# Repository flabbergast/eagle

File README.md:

# flabbergast's [EAGLE](http://www.cadsoftusa.com/eagle-pcb-design-software/?language=en) PCB files

Currently, the following PCBs are here:

## X-A4U stick (rev1 and rev2.1)

An USB stick with atxmega128a4u, RGB LED, microSD socket and 2 buttons.
More details [here](https://flabbergast.github.io/x-a4u-r2/).

## little2wire

My SMD take on [Little Wire](http://littlewire.cc). Optionally 3V3
operation, USB-A or mini or micro USB socket. Webpage
[here](https://flabbergast.github.io/l2w/).

## [AVR stick] microSD + ATMEL EEPROM shield

A shield for matrixstorm's [AVR stick], with micro SD, SOIC-8 (JEDEC)
I2C EEPROM landing and a proto area.
A more detailed writeup is
[here](http://174763.calepin.co/uSD-shield-1.html).

Fits Sparkfun's [microSD socket](https://www.sparkfun.com/products/127),
a variety of ATMEL (or others') I2C EEPROMs (including crypto chips like
[ATSHA204], [ATAES132] or [ATECC108] in SOIC-8 package). One button
(also from [Sparkfun](https://www.sparkfun.com/products/8720)), one LED.
The smaller parts are SMD 1206.

## Small UEXT board with microSD and I2C EEPROM

A simple [UEXT] board, with the same microSD socket from Sparkfun, and a
SOIC-8 I2C EEPROM landing. Note that the boards from [Olimex] with UEXT
already have pull-ups on I2C signals, so these are not needed if it
should be used with them.

## Various breakout_ boards

These are basic breakouts for some ARM chips. Minimal (recommended) extra parts. For photos and some comments see [this post](https://flabbergast.github.io/posts/arm-breakouts/).

## blackmagic-hw

A variation on [Black Magic Probe] Mini V1, based off of [Richard Meadows' variation](https://github.com/richardeoin/blackmagic-hardware/).
See README in the subdirectory for more info.

[AVR stick]: http://matrixstorm.com/avr/avrstick/
[ATSHA204]: http://www.atmel.com/devices/atsha204.aspx
[ATAES132]: http://www.atmel.com/devices/ataes132.aspx
[ATECC108]: http://www.atmel.com/devices/atecc108.aspx
[Olimex]: https://www.olimex.com/
[UEXT]: https://www.olimex.com/Products/Modules/
[Black Magic Probe]: https://black-magic.org/

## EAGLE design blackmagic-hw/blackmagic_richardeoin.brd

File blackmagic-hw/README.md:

# A variation of Black Magic Probe mini V1.0

Started with [Richard Meadows' modification](https://github.com/richardeoin/blackmagic-hardware/) of BMPMV1, summary of that is below.

On top of that, no electrical modifications, only added an option to solder USB micro socket instead of USB mini; and the 10 pin programming header is now through-hole.

# Original README from Richard Meadows

This variant attempts to be as faithful to the Blackmagic mini as
possible, but also has several differences. This board has been built
and functions.

## Details

* The schematic and board have both been designed using Cadsoft EAGLE
  v6.4.0.

* The board size is 40mm x 16mm.

* The programming connector is an ARM 10-PIN Interface as described
  [here](http://www.keil.com/support/man/docs/ulink2/ulink2_hw_connectors.htm).

## Differences

### Uses 0603 [1608 Metric] components

The layout is intended for reflow soldering.

### Includes Level Translator

This board incorporates the same level translator used in the
full-sized Blackmagic, so it can be used to safely program 2.7V or
1.8V systems.

### USART Connector

The STM32F103's USART1 peripheral is broken out into a 0.1"
header. The hole centres are
[slightly offset to allow a press-fit](https://www.sparkfun.com/tutorials/114).

### BOOT0 Button

As well as the standard button for entering USB DFU mode, this variant
also provides a button for pulling the BOOT0 pin high to activate the
STM32 SystemMemory bootloader. Hold this button when plugging in the
module to enter then bootloader mode, over USART1.

This is useful for programming a brand new or 'bricked' blackmagic
with the DFU firmware, the standard DFU mode
should be used for regular firmware updates.

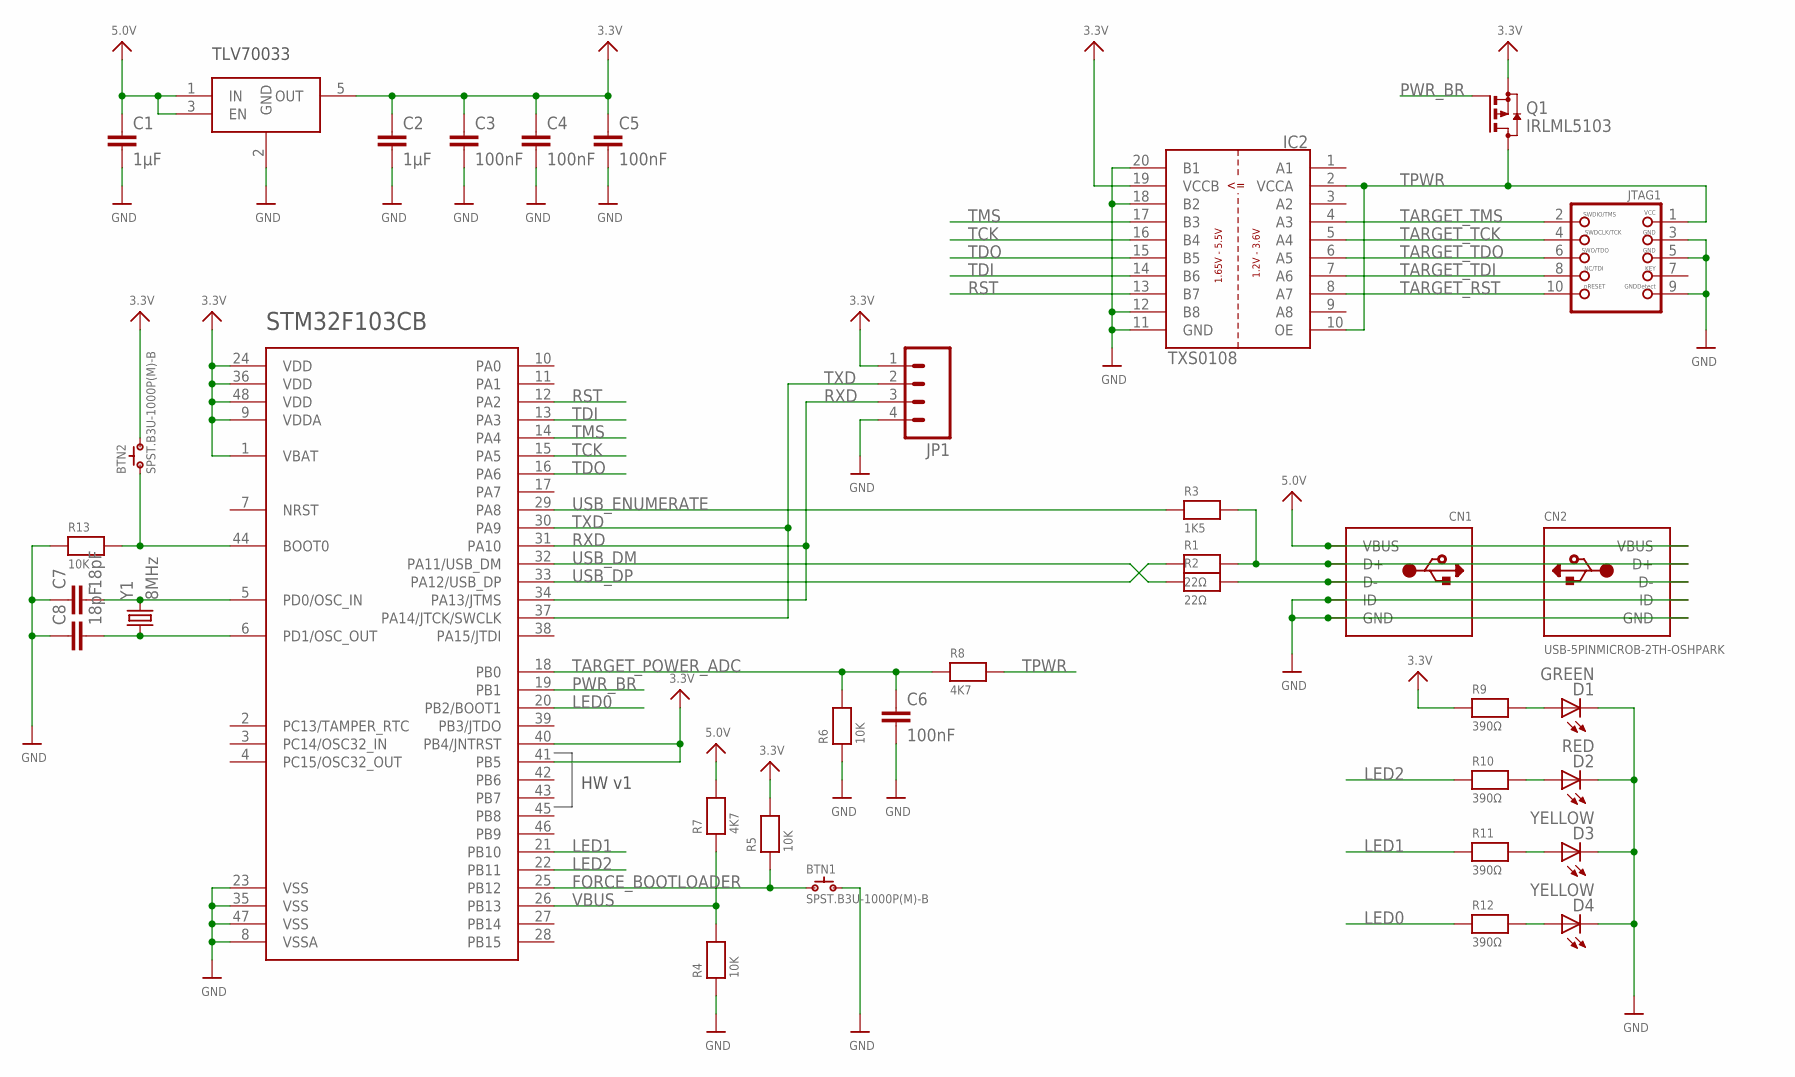
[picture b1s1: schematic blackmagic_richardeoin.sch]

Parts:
BTN1, BTN2: SPST.B3U-1000P(M)-B; B3U-1000P(M)-B
C1, C2: 1µF; C0603K
C3, C4, C5, C6: 100nF; C0603K
C7, C8: 18pF; C0603K
CN1: USBMINIB; USB-MINIB
CN2: USB-5PINMICROB-2TH-OSHPARK; USB-MICROB-2TH-OSHPARK
D1: GREEN; CHIPLED_0603
D2: RED; CHIPLED_0603
D3, D4: YELLOW; CHIPLED_0603
IC1: STM32F_48PIN; TQFP48
IC2: TXS0108; TSSOP20
IC3: TLV70033DCK; SC70-5L
JP1: M04LOCK; 1X04_LOCK
JTAG1: JTAG-CORTEXM3TH; 2X05_1.27MM_TH
Q1: IRLML5103; SOT23
R1, R2: 22Ω; 0603-MINI
R3: 1K5; 0603-MINI
R4, R5, R6, R13: 10K; 0603-MINI
R7, R8: 4K7; 0603-MINI
R9, R10, R11, R12: 390Ω; 0603-MINI
Y1: 8MHz; CRYSTAL-SMD-5X3

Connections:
3.3V: BTN2.2, C2.1, C3.1, C4.1, C5.1, IC1.1 (VBAT), IC1.9 (VDDA), IC1.24 (VDD), IC1.36 (VDD), IC1.40 (PB4/JNTRST), IC1.41 (PB5), IC1.48 (VDD), IC2.19 (VCCB), IC3.5 (OUT), JP1.1, Q1.2 (S), R5.2, R9.1
5.0V: C1.1, CN1.VBUS, CN2.VBUS, IC3.1 (IN), IC3.3 (EN), R7.2
BOOT0: BTN2.1, IC1.44 (BOOT0), R13.2
D+: CN1.D+, CN2.D+, R1.2, R3.2
D-: CN1.D-, CN2.D-, R2.2
FORCE_BOOTLOADER: BTN1.1, IC1.25 (PB12), R5.1
GND: BTN1.2, C1.2, C2.2, C3.2, C4.2, C5.2, C6.2, C7.1, C8.1, CN1.GND, CN1.ID, CN2.GND, CN2.ID, D1.C, D2.C, D3.C, D4.C, IC1.8 (VSSA), IC1.23 (VSS), IC1.35 (VSS), IC1.47 (VSS), IC2.11 (GND), IC2.12 (B8), IC2.18 (B2), IC2.20 (B1), IC3.2 (GND), JP1.4, JTAG1.3, JTAG1.5, JTAG1.9, R4.1, R6.1, R13.1
LED0: IC1.20 (PB2/BOOT1), R12.1
LED1: IC1.21 (PB10), R11.1
LED2: IC1.22 (PB11), R10.1
LPC_XTAL2: C8.2, IC1.6 (PD1/OSC_OUT), Y1.1
unnamed: D2.A, R10.2
unnamed: D1.A, R9.2
unnamed: D3.A, R11.2
unnamed: D4.A, R12.2
OSC_IN: C7.2, IC1.5 (PD0/OSC_IN), Y1.3 (2)
PWR_BR: IC1.19 (PB1), Q1.1 (G)
RST: IC1.12 (PA2), IC2.13 (B7)
RXD: IC1.31 (PA10), IC1.34 (PA13/JTMS), JP1.3
TARGET_POWER_ADC: C6.1, IC1.18 (PB0), R6.2, R8.1
TARGET_RST: IC2.8 (A7), JTAG1.10
TARGET_TCK: IC2.5 (A4), JTAG1.4
TARGET_TDI: IC2.7 (A6), JTAG1.8
TARGET_TDO: IC2.6 (A5), JTAG1.6
TARGET_TMS: IC2.4 (A3), JTAG1.2
TCK: IC1.15 (PA5), IC2.16 (B4)
TDI: IC1.13 (PA3), IC2.14 (B6)
TDO: IC1.16 (PA6), IC2.15 (B5)
TMS: IC1.14 (PA4), IC2.17 (B3)
TPWR: IC2.2 (VCCA), IC2.10 (OE), JTAG1.1, Q1.3 (D), R8.2
TXD: IC1.30 (PA9), IC1.37 (PA14/JTCK/SWCLK), JP1.2
USB_DM: IC1.32 (PA11/USB_DM), R2.1
USB_DP: IC1.33 (PA12/USB_DP), R1.1
USB_ENUMERATE: IC1.29 (PA8), R3.1
VBUS: IC1.26 (PB13), R4.2, R7.1

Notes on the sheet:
STM32F103CB
HW v1
TLV70033

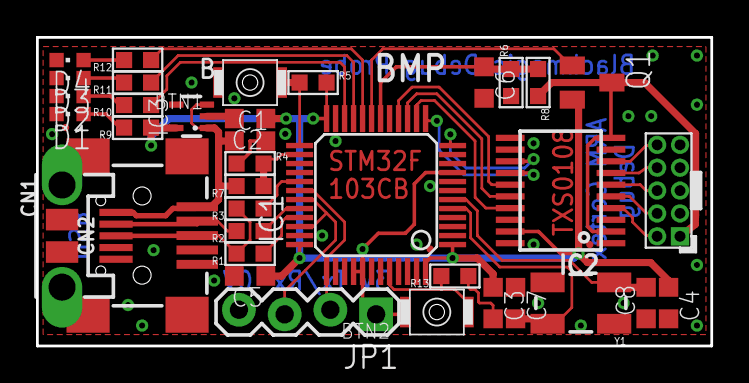
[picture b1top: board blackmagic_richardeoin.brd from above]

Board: 2 copper layers, 37.5 x 17.1 mm, 36 parts (0 on the bottom side), 35 nets.

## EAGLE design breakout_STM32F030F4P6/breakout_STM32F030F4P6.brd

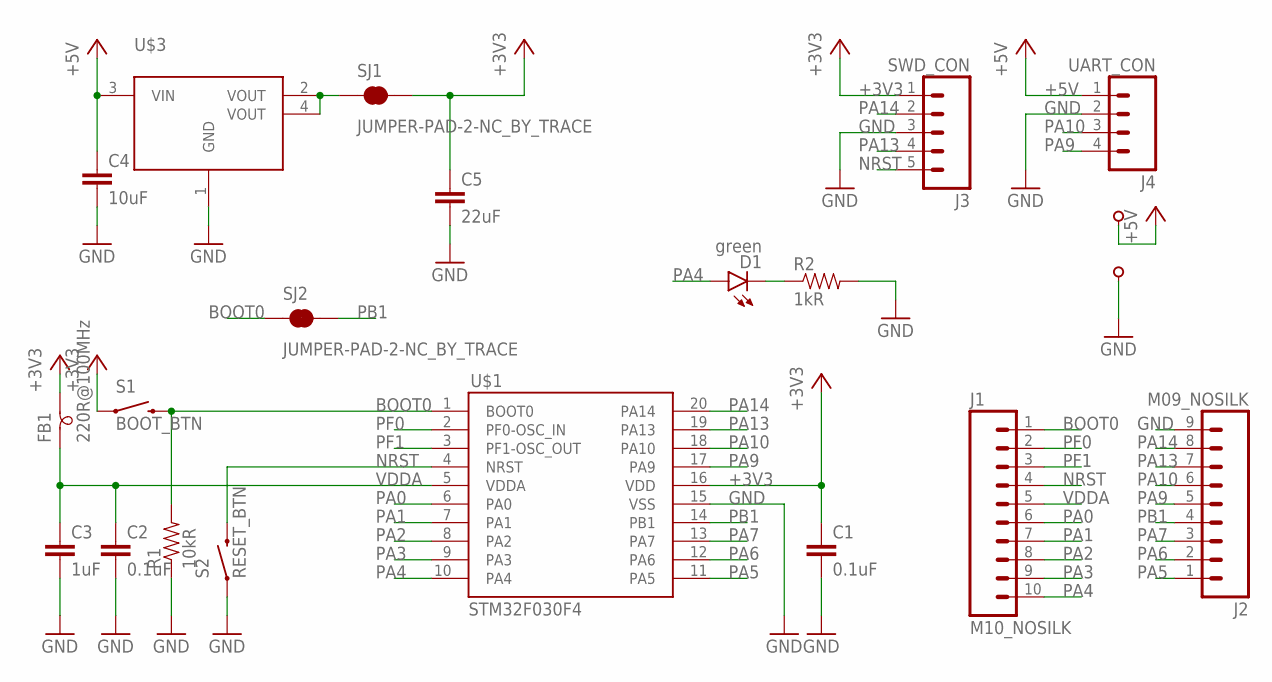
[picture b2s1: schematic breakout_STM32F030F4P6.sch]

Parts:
C1, C2: 0.1uF; 0805
C3: 1uF; 0805
C4: 10uF; 0805
C5: 22uF; 0805
D1: green; LED-805
FB1: 220R@100MHz; 0805
J1: M10_NOSILK
J2: M09_NOSILK
J3: SWD_CON; M05_NOSILK_1SQ
J4: UART_CON; M04_NOSILK_1SQ
R1: 10kR; 0805
R2: 1kR; 0805
S1: BOOT_BTN; TACTILE-SWITCH-1101NE
S2: RESET_BTN; TACTILE-SWITCH-1101NE
SJ1, SJ2: JUMPER-PAD-2-NC_BY_TRACE; PAD-JUMPER-2-NC_BY_TRACE_YES_SILK
U$1: STM32F030F4; TSSOP-20
U$2: M01_1SQ
U$3: AMS1117_SOT223; SOT223
U$4: M01_NOSILK

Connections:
+3V3: C1.1, C5.1, FB1.2, J3.1, S1.1, SJ1.2, U$1.16 (VDD)
+5V: C4.1, J4.1, U$2.1, U$3.3 (VIN)
BOOT0: J1.1, R1.2, S1.2, SJ2.1, U$1.1 (BOOT0)
GND: C1.2, C2.2, C3.2, C4.2, C5.2, J2.9, J3.3, J4.2, R1.1, R2.2, S2.1, U$1.15 (VSS), U$3.1 (GND), U$4.1
unnamed: SJ1.1, U$3.2 (VOUT), U$3.4 (VOUT)
unnamed: D1.C, R2.1
NRST: J1.4, J3.5, S2.2, U$1.4 (NRST)
PA0: J1.6, U$1.6 (PA0)
PA1: J1.7, U$1.7 (PA1)
PA2: J1.8, U$1.8 (PA2)
PA3: J1.9, U$1.9 (PA3)
PA4: D1.A, J1.10, U$1.10 (PA4)
PA5: J2.1, U$1.11 (PA5)
PA6: J2.2, U$1.12 (PA6)
PA7: J2.3, U$1.13 (PA7)
PA9: J2.5, J4.4, U$1.17 (PA9)
PA10: J2.6, J4.3, U$1.18 (PA10)
PA13: J2.7, J3.4, U$1.19 (PA13)
PA14: J2.8, J3.2, U$1.20 (PA14)
PB1: J2.4, SJ2.2, U$1.14 (PB1)
PF0: J1.2, U$1.2 (PF0-OSC_IN)
PF1: J1.3, U$1.3 (PF1-OSC_OUT)
VDDA: C2.1, C3.1, FB1.1, J1.5, U$1.5 (VDDA)

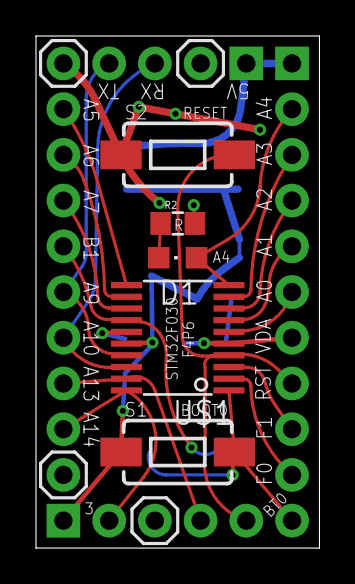
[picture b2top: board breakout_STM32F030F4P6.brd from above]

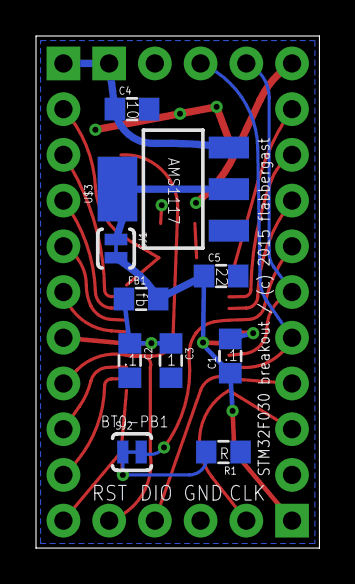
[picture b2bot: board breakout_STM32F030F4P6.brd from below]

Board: 2 copper layers, 15.7 x 28.4 mm, 21 parts (10 on the bottom side), 23 nets.

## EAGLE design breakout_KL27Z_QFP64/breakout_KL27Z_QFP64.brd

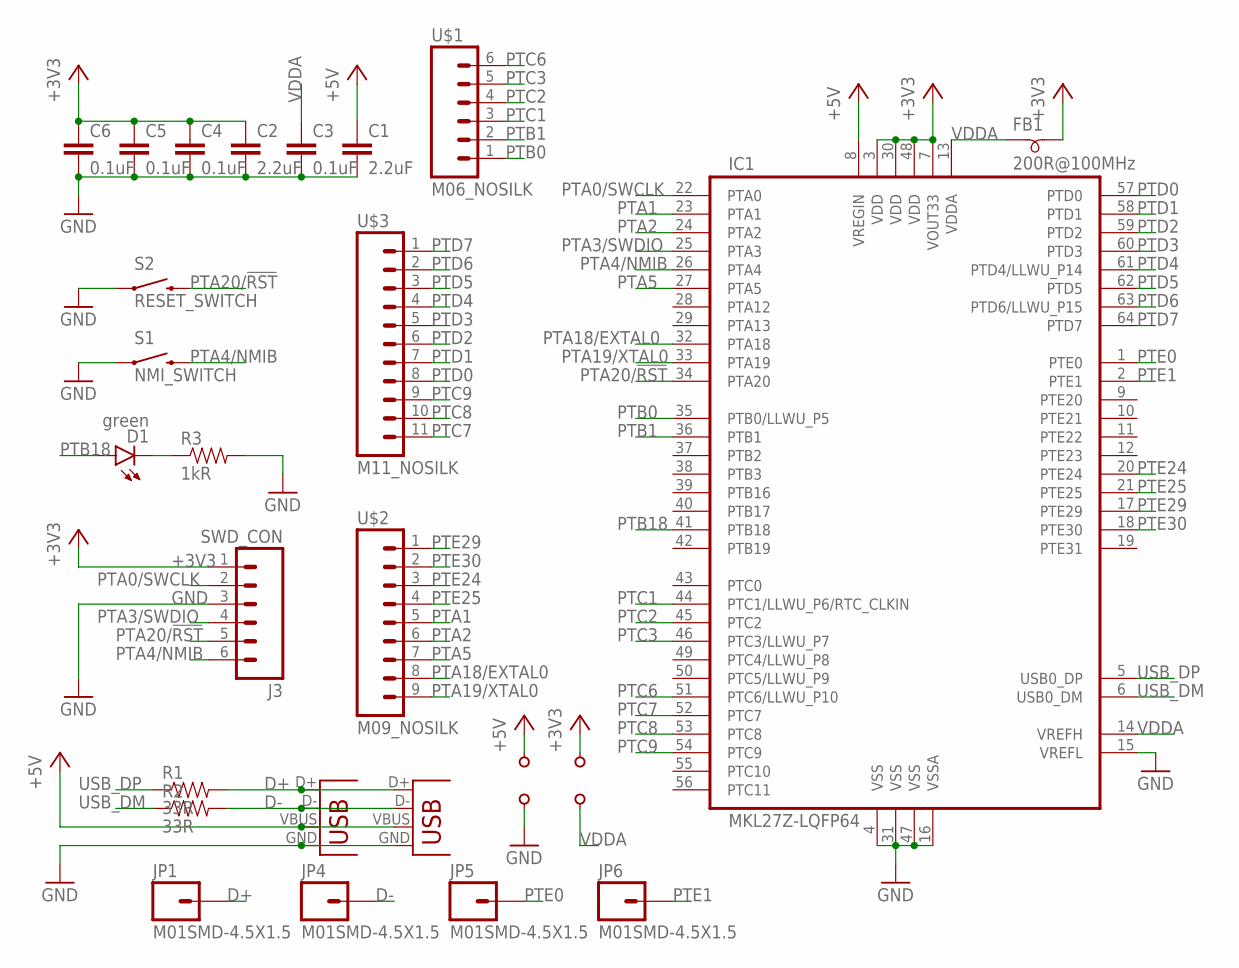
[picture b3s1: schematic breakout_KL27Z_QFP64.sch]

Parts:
C1, C2: 2.2uF; 0805
C3, C4, C5, C6: 0.1uF; 0805
D1: green; LED-805
FB1: 200R@100MHz; 0805
IC1: MKL27Z-LQFP64; TQFP-64-0.5
J3: SWD_CON; M06_NOSILK_1SQ
JP1, JP4, JP5, JP6: M01SMD-4.5X1.5; PAD-1.5X4.5
JP2: USBSMD; USB-MINIB
JP3: USB-MICROB
R1, R2: 33R; 0805
R3: 1kR; 0805
S1: NMI_SWITCH; TACTILE-SWITCH-SMD
S2: RESET_SWITCH; TACTILE-SWITCH-SMD
U$1: M06_NOSILK
U$2: M09_NOSILK
U$3: M11_NOSILK
U$4, U$5, U$7: M01_1SQ
U$6: M01_NOSILK

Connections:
+3V3: C2.1, C4.1, C5.1, C6.1, FB1.2, IC1.3 (VDD), IC1.7 (VOUT33), IC1.30 (VDD), IC1.48 (VDD), J3.1, U$5.1
+5V: C1.1, IC1.8 (VREGIN), JP2.VBUS, JP3.VBUS, U$4.1
D+: JP1.P$1, JP2.D+, JP3.D+, R1.2
D-: JP2.D-, JP3.D-, JP4.P$1, R2.2
GND: C1.2, C2.2, C3.2, C4.2, C5.2, C6.2, IC1.4 (VSS), IC1.15 (VREFL), IC1.16 (VSSA), IC1.31 (VSS), IC1.47 (VSS), J3.3, JP2.GND, JP3.GND, R3.2, S1.1, S1.2 (1), S2.1, S2.2 (1), U$6.1
unnamed: D1.C, R3.1
PTA0/SWCLK: IC1.22 (PTA0), J3.2
PTA1: IC1.23 (PTA1), U$2.5
PTA2: IC1.24 (PTA2), U$2.6
PTA3/SWDIO: IC1.25 (PTA3), J3.4
PTA4/NMIB: IC1.26 (PTA4), J3.6, S1.3 (2), S1.4 (2)
PTA5: IC1.27 (PTA5), U$2.7
PTA18/EXTAL0: IC1.32 (PTA18), U$2.8
PTA19/XTAL0: IC1.33 (PTA19), U$2.9
PTA20/!RST: IC1.34 (PTA20), J3.5, S2.3 (2), S2.4 (2)
PTB0: IC1.35 (PTB0/LLWU_P5), U$1.1
PTB1: IC1.36 (PTB1), U$1.2
PTB18: D1.A, IC1.41 (PTB18)
PTC1: IC1.44 (PTC1/LLWU_P6/RTC_CLKIN), U$1.3
PTC2: IC1.45 (PTC2), U$1.4
PTC3: IC1.46 (PTC3/LLWU_P7), U$1.5
PTC6: IC1.51 (PTC6/LLWU_P10), U$1.6
PTC7: IC1.52 (PTC7), U$3.11
PTC8: IC1.53 (PTC8), U$3.10
PTC9: IC1.54 (PTC9), U$3.9
PTD0: IC1.57 (PTD0), U$3.8
PTD1: IC1.58 (PTD1), U$3.7
PTD2: IC1.59 (PTD2), U$3.6
PTD3: IC1.60 (PTD3), U$3.5
PTD4: IC1.61 (PTD4/LLWU_P14), U$3.4
PTD5: IC1.62 (PTD5), U$3.3
PTD6: IC1.63 (PTD6/LLWU_P15), U$3.2
PTD7: IC1.64 (PTD7), U$3.1
PTE0: IC1.1 (PTE0), JP5.P$1
PTE1: IC1.2 (PTE1), JP6.P$1
PTE24: IC1.20 (PTE24), U$2.3
PTE25: IC1.21 (PTE25), U$2.4
PTE29: IC1.17 (PTE29), U$2.1
PTE30: IC1.18 (PTE30), U$2.2
USB_DM: IC1.6 (USB0_DM), R2.1
USB_DP: IC1.5 (USB0_DP), R1.1
VDDA: C3.1, FB1.1, IC1.13 (VDDA), IC1.14 (VREFH), U$7.1

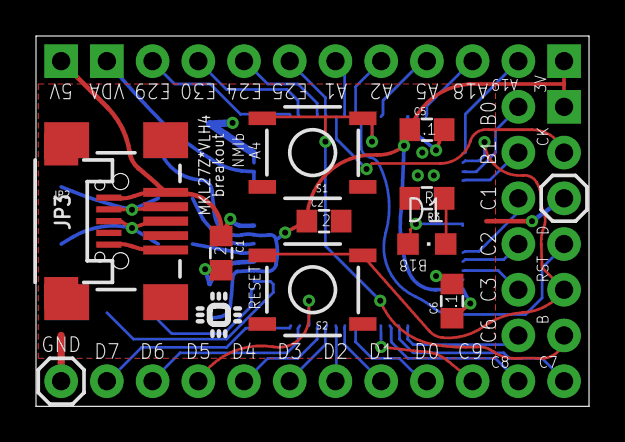
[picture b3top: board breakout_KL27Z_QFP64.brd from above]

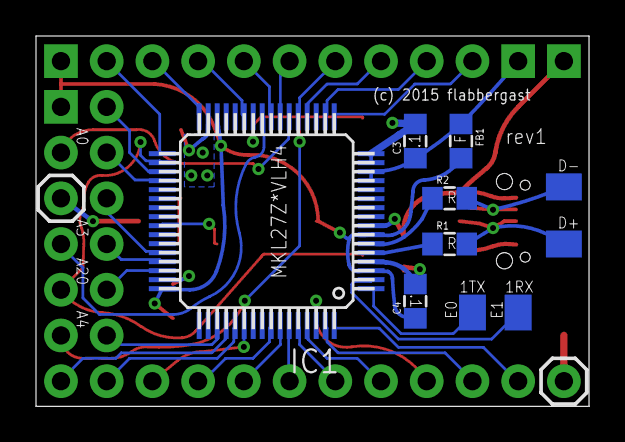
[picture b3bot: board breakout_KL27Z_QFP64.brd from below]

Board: 2 copper layers, 30.7 x 20.6 mm, 29 parts (10 on the bottom side), 42 nets.

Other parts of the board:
U$8: IC_TINY

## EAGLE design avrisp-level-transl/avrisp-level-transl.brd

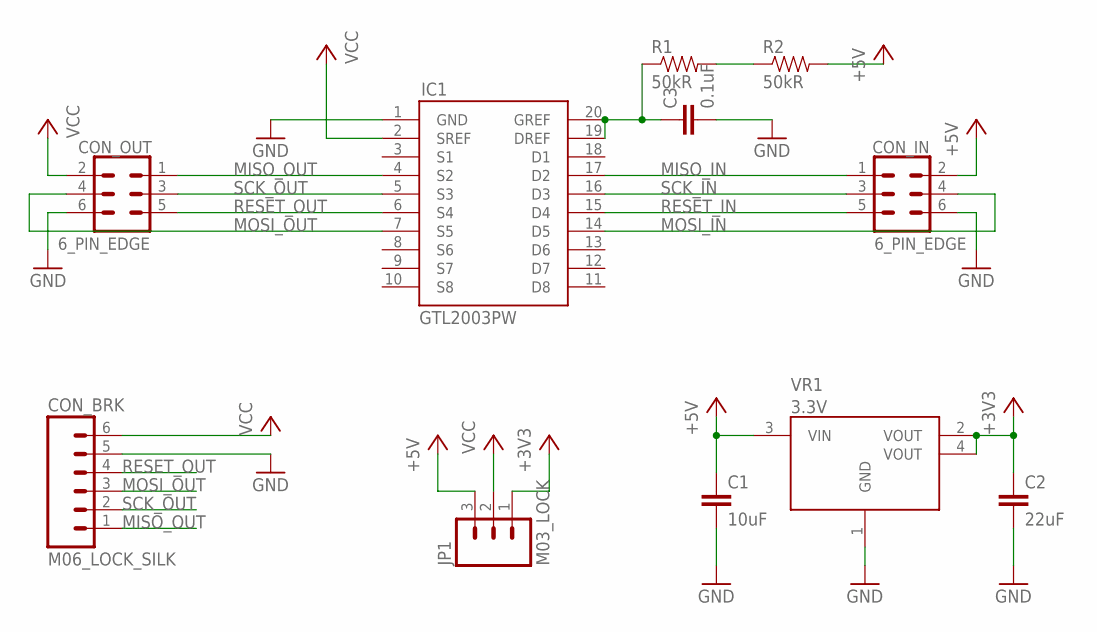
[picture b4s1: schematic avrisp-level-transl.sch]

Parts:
C1: 10uF; 0805
C2: 22uF; 0805
C3: 0.1uF; 0805
CON_BRK: M06_LOCK_SILK
CON_IN: 6_PIN_EDGE
CON_OUT: 6_PIN_EDGE
IC1: GTL2003PW; TSSOP-20
JP1: M03_LOCK
R1, R2: 50kR; 0805
VR1: 3.3V; SOT223

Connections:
+3V3: C2.1, JP1.1, VR1.2 (VOUT), VR1.4 (VOUT)
+5V: C1.1, CON_IN.2, JP1.3, R2.2, VR1.3 (VIN)
GND: C1.2, C2.2, C3.2, CON_BRK.5, CON_IN.6, CON_OUT.6, IC1.1 (GND), VR1.1 (GND)
MISO_IN: CON_IN.1, IC1.17 (D2)
MISO_OUT: CON_BRK.1, CON_OUT.1, IC1.4 (S2)
MOSI_IN: CON_IN.4, IC1.14 (D5)
MOSI_OUT: CON_BRK.3, CON_OUT.4, IC1.7 (S5)
unnamed: C3.1, IC1.19 (DREF), IC1.20 (GREF), R1.1
unnamed: R1.2, R2.1
RESET_IN: CON_IN.5, IC1.15 (D4)
RESET_OUT: CON_BRK.4, CON_OUT.5, IC1.6 (S4)
SCK_IN: CON_IN.3, IC1.16 (D3)
SCK_OUT: CON_BRK.2, CON_OUT.3, IC1.5 (S3)
VCC: CON_BRK.6, CON_OUT.2, IC1.2 (SREF), JP1.2

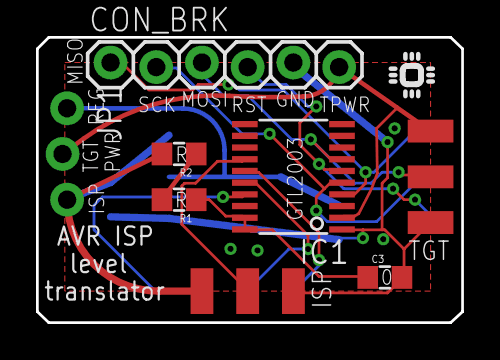
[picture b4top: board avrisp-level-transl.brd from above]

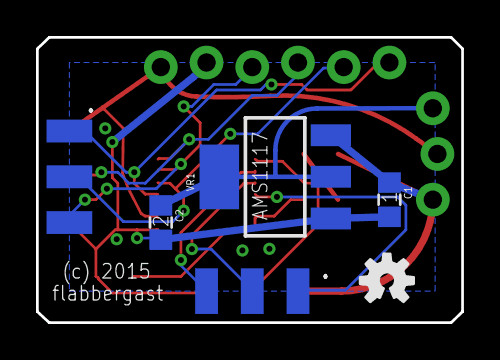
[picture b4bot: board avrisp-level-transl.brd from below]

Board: 2 copper layers, 23.6 x 15.8 mm, 13 parts (6 on the bottom side), 14 nets.

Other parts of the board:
U$1: IC_TINY
U$2: OSHW-LOGO-S

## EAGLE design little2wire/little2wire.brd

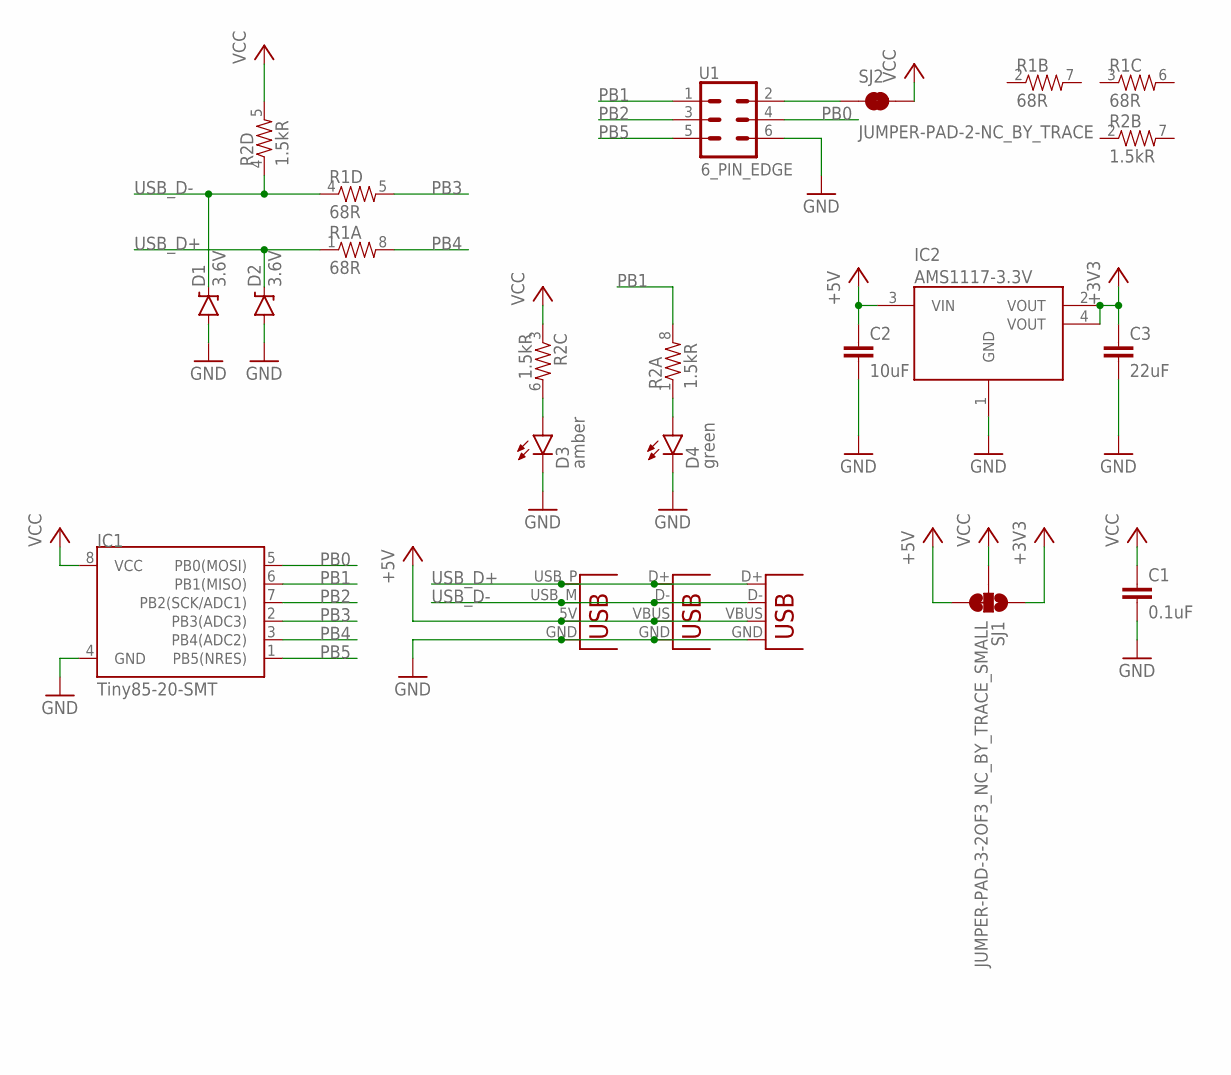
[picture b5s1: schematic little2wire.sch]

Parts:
C1: 0.1uF; 0805
C2: 10uF; 0805
C3: 22uF; 0805
D1, D2: 3.6V; SOD-323
D3: amber; LED-805
D4: green; LED-805
IC1: Tiny85-20-SMT; SO08-EIAJ
IC2: AMS1117-3.3V; SOT223
JP1: USBPCB; USB-A-PCB
JP2: USBSMD; USB-MINIB
JP3: USB-MICROB
R1: 68R; 1206-ARRAY
R2: 1.5kR; 1206-ARRAY
SJ1: JUMPER-PAD-3-2OF3_NC_BY_TRACE_SMALL; PAD-JUMPER-3-2OF3_NC_BY_TRACE_YES_SILK_FULL_BOX
SJ2: JUMPER-PAD-2-NC_BY_TRACE; PAD-JUMPER-2-NC_BY_TRACE_YES_SILK
U1: 6_PIN_EDGE

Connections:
+3V3: C3.1, IC2.2 (VOUT), IC2.4 (VOUT), SJ1.1
+5V: C2.1, IC2.3 (VIN), JP1.5V (VBUS), JP2.VBUS, JP3.VBUS, SJ1.3
GND: C1.2, C2.2, C3.2, D1.A, D2.A, D3.C, D4.C, IC1.4 (GND), IC2.1 (GND), JP1.GND, JP2.GND, JP3.GND, U1.6
unnamed: D4.A, R2.1
unnamed: D3.A, R2.6 (2)
unnamed: SJ2.1, U1.2
PB0: IC1.5 (PB0(MOSI)), U1.4
PB1: IC1.6 (PB1(MISO)), R2.8 (2), U1.1
PB2: IC1.7 (PB2(SCK/ADC1)), U1.3
PB3: IC1.2 (PB3(ADC3)), R1.5 (2)
PB4: IC1.3 (PB4(ADC2)), R1.8 (2)
PB5: IC1.1 (PB5(NRES)), U1.5
USB_D+: D2.C, JP1.USB_P (D+), JP2.D+, JP3.D+, R1.1
USB_D-: D1.C, JP1.USB_M (D-), JP2.D-, JP3.D-, R1.4 (1), R2.4 (1)
VCC: C1.1, IC1.8 (VCC), R2.3 (1), R2.5 (2), SJ1.2, SJ2.2

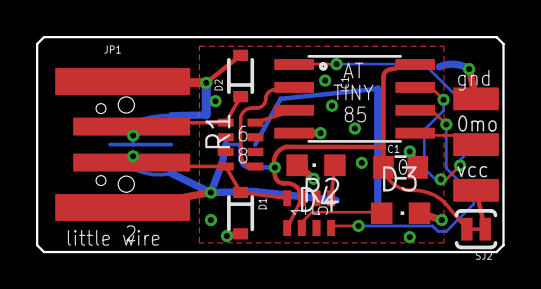
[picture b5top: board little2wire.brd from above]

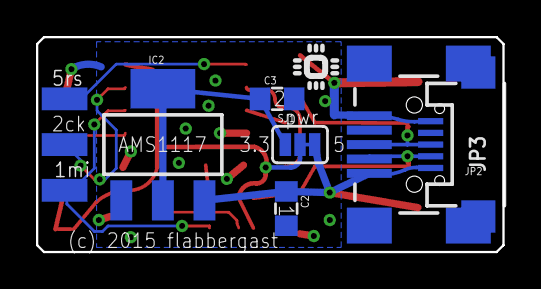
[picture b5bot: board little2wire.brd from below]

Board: 2 copper layers, 25.9 x 11.9 mm, 18 parts (8 on the bottom side), 15 nets.

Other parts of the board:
U$1: IC_TINY

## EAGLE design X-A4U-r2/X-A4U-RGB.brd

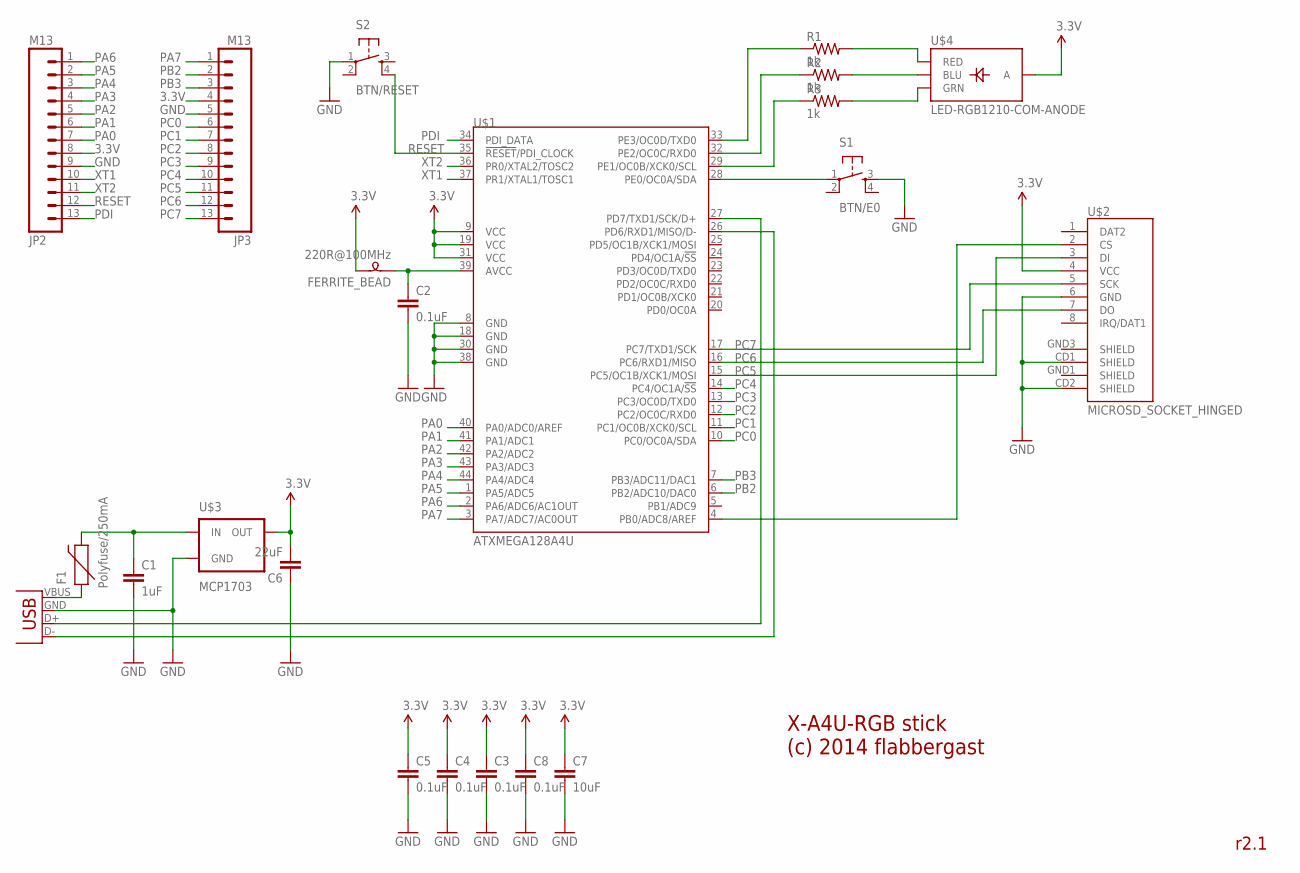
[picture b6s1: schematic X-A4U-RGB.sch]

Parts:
C1: 1uF; 0805
C2, C3, C4, C5: 0.1uF; 0805
C6: 22uF; 1206
C7: 10uF; 1206
C8: 0.1uF; 1206
F1: Polyfuse/250mA; PTC-1206-WIDE
FERRITE_BEAD: 220R@100MHz; 0805
JP1: USB-A-H
JP2, JP3: M13; 1X13
R1, R2, R3: 1k; 0805
S1: BTN/E0; TACTILE-SWITCH-SMD
S2: BTN/RESET; TACTILE-SWITCH-SMD
U$1: ATXMEGA128A4U; TQFP-44
U$2: MICROSD_SOCKET_HINGED; MICROSD_SOCKET_SLIDE
U$3: MCP1703; SOT-89
U$4: LED-RGB1210-COM-ANODE; LED-RGB-1210

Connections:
3.3V: C3.1, C4.1, C5.1, C6.2, C7.1, C8.1, FERRITE_BEAD.2, JP2.8, JP3.4, U$1.9 (VCC), U$1.19 (VCC), U$1.31 (VCC), U$2.4 (VCC), U$3.3 (OUT), U$4.A
GND: C1.2, C2.2, C3.2, C4.2, C5.2, C6.1, C7.2, C8.2, JP1.GND (VBUS), JP2.9, JP3.5, S1.3, S2.1, U$1.8 (GND), U$1.18 (GND), U$1.30 (GND), U$1.38 (GND), U$2.6 (GND), U$2.CD1 (SHIELD), U$2.CD2 (SHIELD), U$3.1 (GND)
unnamed: JP1.D+ (D-), U$1.27 (PD7/TXD1/SCK/D+)
unnamed: JP1.D- (D+), U$1.26 (PD6/RXD1/MISO/D-)
unnamed: F1.1, JP1.VBUS (GND)
unnamed: R3.1, U$1.29 (PE1/OC0B/XCK0/SCL)
unnamed: S1.1, U$1.28 (PE0/OC0A/SDA)
unnamed: C2.1, FERRITE_BEAD.1, U$1.39 (AVCC)
unnamed: U$1.4 (PB0/ADC8/AREF), U$2.2 (CS)
unnamed: R2.1, U$1.32 (PE2/OC0C/RXD0)
unnamed: R1.1, U$1.33 (PE3/OC0D/TXD0)
unnamed: R1.2, U$4.R (RED)
unnamed: R3.2, U$4.G (GRN)
unnamed: R2.2, U$4.B (BLU)
PA0: JP2.7, U$1.40 (PA0/ADC0/AREF)
PA1: JP2.6, U$1.41 (PA1/ADC1)
PA2: JP2.5, U$1.42 (PA2/ADC2)
PA3: JP2.4, U$1.43 (PA3/ADC3)
PA4: JP2.3, U$1.44 (PA4/ADC4)
PA5: JP2.2, U$1.1 (PA5/ADC5)
PA6: JP2.1, U$1.2 (PA6/ADC6/AC1OUT)
PA7: JP3.1, U$1.3 (PA7/ADC7/AC0OUT)
PB2: JP3.2, U$1.6 (PB2/ADC10/DAC0)
PB3: JP3.3, U$1.7 (PB3/ADC11/DAC1)
PC0: JP3.6, U$1.10 (PC0/OC0A/SDA)
PC1: JP3.7, U$1.11 (PC1/OC0B/XCK0/SCL)
PC2: JP3.8, U$1.12 (PC2/OC0C/RXD0)
PC3: JP3.9, U$1.13 (PC3/OC0D/TXD0)
PC4: JP3.10, U$1.14 (PC4/OC1A/!SS!)
PC5: JP3.11, U$1.15 (PC5/OC1B/XCK1/MOSI), U$2.3 (DI)
PC6: JP3.12, U$1.16 (PC6/RXD1/MISO), U$2.7 (DO)
PC7: JP3.13, U$1.17 (PC7/TXD1/SCK), U$2.5 (SCK)
PDI: JP2.13, U$1.34 (PDI_DATA)
RESET: JP2.12, S2.4, U$1.35 (!RESET!/PDI_CLOCK)
VBUS: C1.1, F1.2, U$3.2 (IN), U$3.4 (IN)
XT1: JP2.10, U$1.37 (PR1/XTAL1/TOSC1)
XT2: JP2.11, U$1.36 (PR0/XTAL2/TOSC2)

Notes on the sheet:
X-A4U-RGB stick (c) 2014 flabbergast

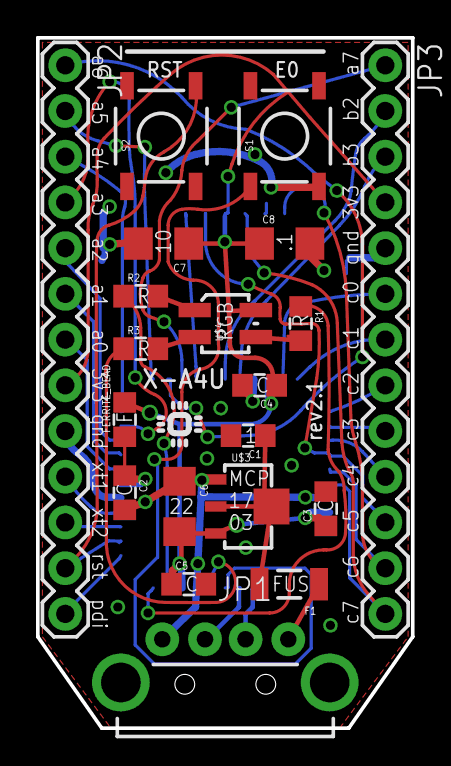
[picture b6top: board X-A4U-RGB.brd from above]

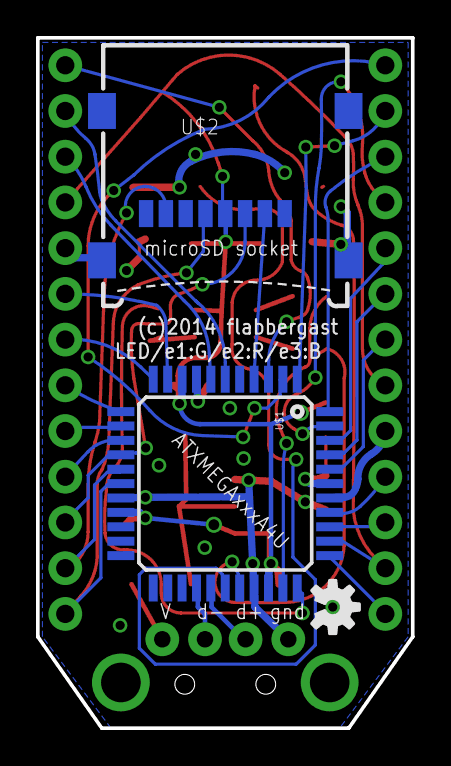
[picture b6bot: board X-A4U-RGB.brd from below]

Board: 2 copper layers, 20.8 x 38.4 mm, 24 parts (3 on the bottom side), 37 nets.

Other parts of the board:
U$5: OSHW-LOGO-S
U$6: IC_TINY

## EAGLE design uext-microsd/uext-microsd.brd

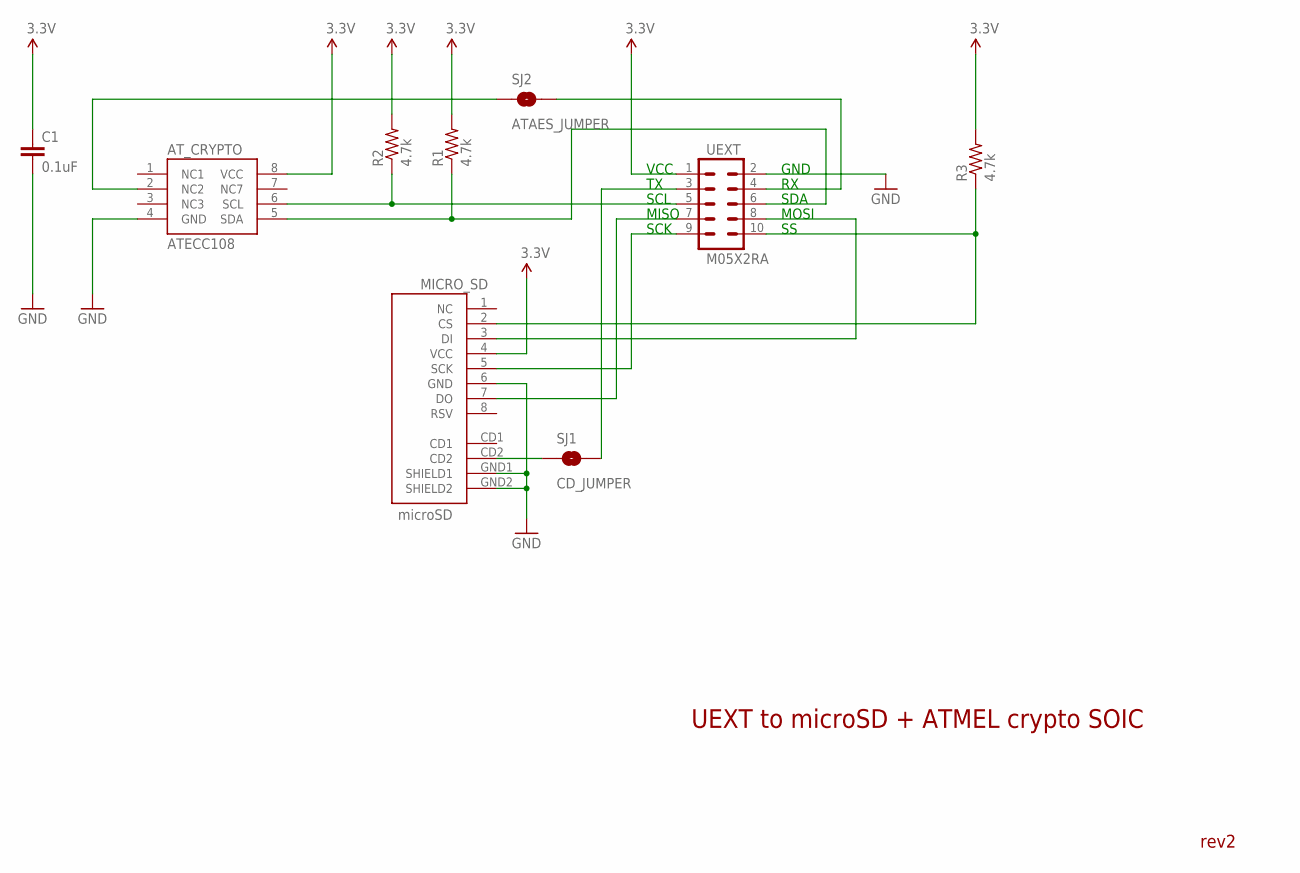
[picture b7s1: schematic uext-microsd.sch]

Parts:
AT_CRYPTO: ATECC108; SOIC8
C1: 0.1uF; 1206
MICRO_SD: microSD; MICRO-SD-SOCKET-PP
R1, R2, R3: 4.7k; 1206
SJ1: CD_JUMPER; PAD-JUMPER-2-NO_YES_SILK
SJ2: ATAES_JUMPER; PAD-JUMPER-2-NO_YES_SILK
UEXT: M05X2RA; 2X5-RA

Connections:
3.3V: AT_CRYPTO.8 (VCC), C1.1, MICRO_SD.4 (VCC), R1.2, R2.2, R3.2, UEXT.1
GND: AT_CRYPTO.4 (GND), C1.2, MICRO_SD.6 (GND), MICRO_SD.GND1 (SHIELD1), MICRO_SD.GND2 (SHIELD2), UEXT.2
unnamed: MICRO_SD.5 (SCK), UEXT.9
unnamed: MICRO_SD.3 (DI), UEXT.8
unnamed: MICRO_SD.7 (DO), UEXT.7
unnamed: MICRO_SD.2 (CS), R3.1, UEXT.10
unnamed: SJ1.2, UEXT.3
unnamed: AT_CRYPTO.6 (SCL), R2.1, UEXT.5
unnamed: AT_CRYPTO.5 (SDA), R1.1, UEXT.6
unnamed: SJ2.2, UEXT.4
unnamed: AT_CRYPTO.2 (NC2), SJ2.1
unnamed: MICRO_SD.CD2, SJ1.1

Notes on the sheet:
UEXT to microSD + ATMEL crypto SOIC
SCL
SDA
MISO
MOSI
SCK
VCC
GND

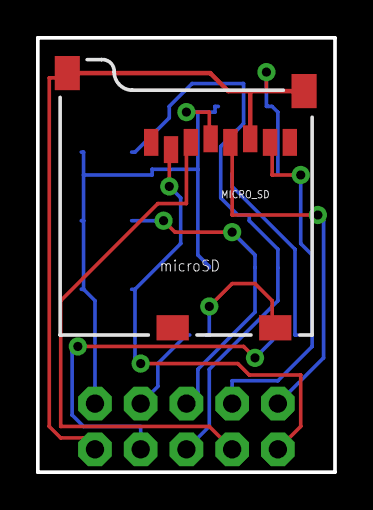
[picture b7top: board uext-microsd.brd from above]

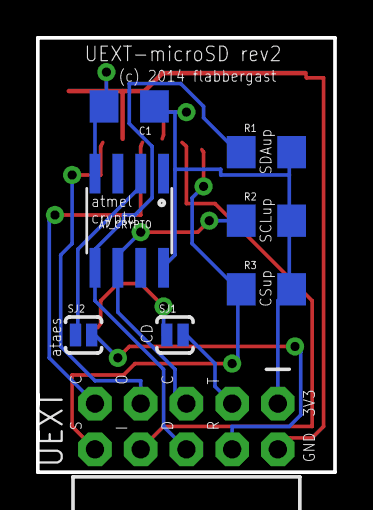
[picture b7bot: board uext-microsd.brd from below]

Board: 2 copper layers, 16.5 x 24.1 mm, 9 parts (8 on the bottom side), 12 nets.

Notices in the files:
avrisp-level-transl/avrisp-level-transl.brd:
(c) 2015
breakout_KL27Z_QFP64/breakout_KL27Z_QFP64.brd:
(c) 2015 flabbergast
breakout_STM32F030F4P6/breakout_STM32F030F4P6.brd:
STM32F030 breakout / (c) 2015 flabbergast
parts and their libraries:
SparkFun-Connectors: Licensing: Creative Commons ShareAlike 4.0 International - https://creativecommons.org/licenses/by-sa/4.0
SparkFun-Aesthetics: Licensing: CC v3.0 Share-Alike You are welcome to use this library for commercial purposes.
